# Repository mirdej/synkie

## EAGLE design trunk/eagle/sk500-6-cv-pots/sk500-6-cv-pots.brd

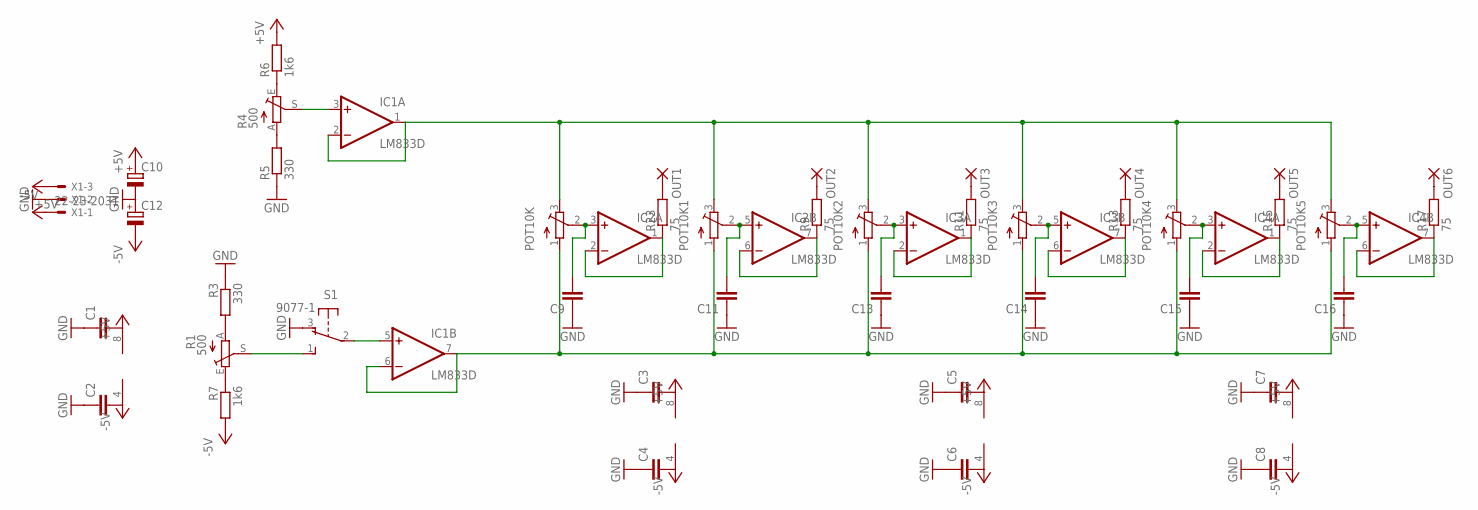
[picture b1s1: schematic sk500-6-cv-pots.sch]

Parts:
C1, C2, C3, C4, C5, C6, C7, C8, C9, C11, C13, C14, C15, C16: C-EUC1206; C1206
C10, C12: CPOL-EUCT6032; CT6032
IC1, IC2, IC3, IC4: LM833D; SO08
OUT1, OUT2, OUT3, OUT4, OUT5, OUT6: 3,17/1,1
POT10K, POT10K1, POT10K2, POT10K3, POT10K4, POT10K5: 10k; ALPS_RK09K111_H
R1, R4: 500; B64W
R3, R5: 330; R1206
R6, R7: 1k6; R1206
R9, R11, R13, R15, R17, R23: 75; R1206
S1: 9077-1
X1: 22-23-2031

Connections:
+5V: C1.2, C3.2, C5.2, C7.2, C10.+, IC1.8 (V+), IC2.8 (V+), IC3.8 (V+), IC4.8 (V+), R6.2, X1.3
-5V: C2.2, C4.2, C6.2, C8.2, C12.-, IC1.4 (V-), IC2.4 (V-), IC3.4 (V-), IC4.4 (V-), R7.2, X1.1
GND: C1.1, C2.1, C3.1, C4.1, C5.1, C6.1, C7.1, C8.1, C9.1, C10.-, C11.1, C12.+, C13.1, C14.1, C15.1, C16.1, R3.1, R5.1, S1.3 (O), X1.2
unnamed: IC1.5 (+IN), S1.2
unnamed: C9.2, IC2.3 (+IN), POT10K.2 (W)
unnamed: R1.A, R3.2
unnamed: R1.E, R7.1
unnamed: R1.S, S1.1 (S)
unnamed: R4.A, R5.2
unnamed: R4.E, R6.1
unnamed: IC1.3 (+IN), R4.S
unnamed: IC1.1 (OUT), IC1.2 (-IN), POT10K.3 (E), POT10K1.3 (E), POT10K2.3 (E), POT10K3.3 (E), POT10K4.3 (E), POT10K5.3 (E)
unnamed: IC2.1 (OUT), IC2.2 (-IN), R23.1
unnamed: OUT2.1, R9.2
unnamed: OUT3.1, R11.2
unnamed: IC2.6 (-IN), IC2.7 (OUT), R9.1
unnamed: IC3.1 (OUT), IC3.2 (-IN), R11.1
unnamed: OUT4.1, R13.2
unnamed: OUT1.1, R23.2
unnamed: IC3.6 (-IN), IC3.7 (OUT), R13.1
unnamed: C11.2, IC2.5 (+IN), POT10K1.2 (W)
unnamed: C13.2, IC3.3 (+IN), POT10K2.2 (W)
unnamed: OUT5.1, R15.2
unnamed: C14.2, IC3.5 (+IN), POT10K3.2 (W)
unnamed: IC4.1 (OUT), IC4.2 (-IN), R15.1
unnamed: IC1.6 (-IN), IC1.7 (OUT), POT10K.1 (S), POT10K1.1 (S), POT10K2.1 (S), POT10K3.1 (S), POT10K4.1 (S), POT10K5.1 (S)
unnamed: OUT6.1, R17.2
unnamed: IC4.6 (-IN), IC4.7 (OUT), R17.1
unnamed: C15.2, IC4.3 (+IN), POT10K4.2 (W)
unnamed: C16.2, IC4.5 (+IN), POT10K5.2 (W)

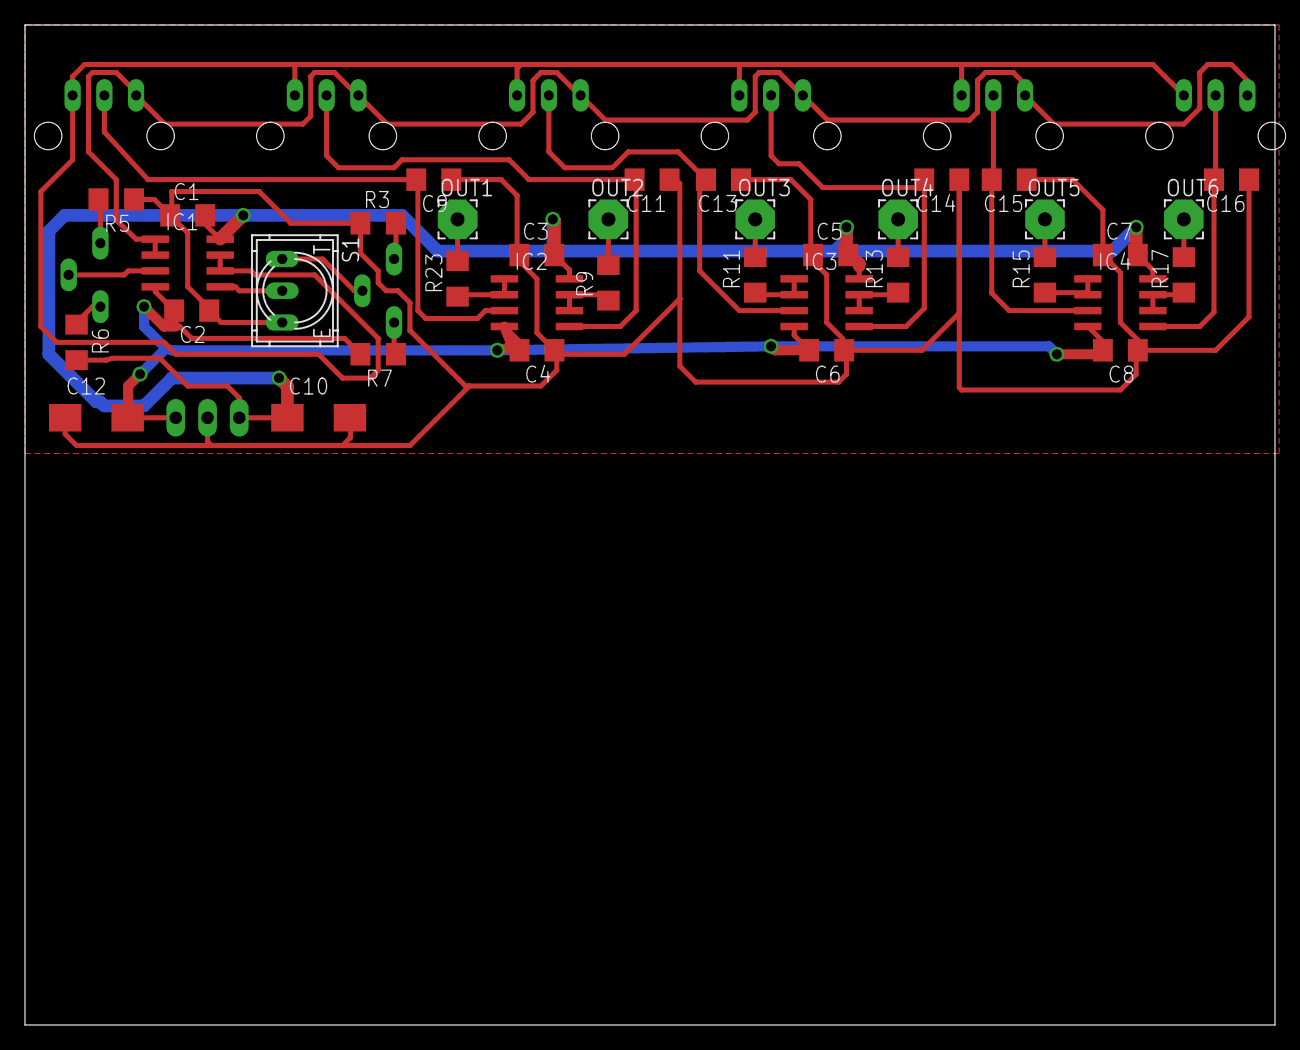
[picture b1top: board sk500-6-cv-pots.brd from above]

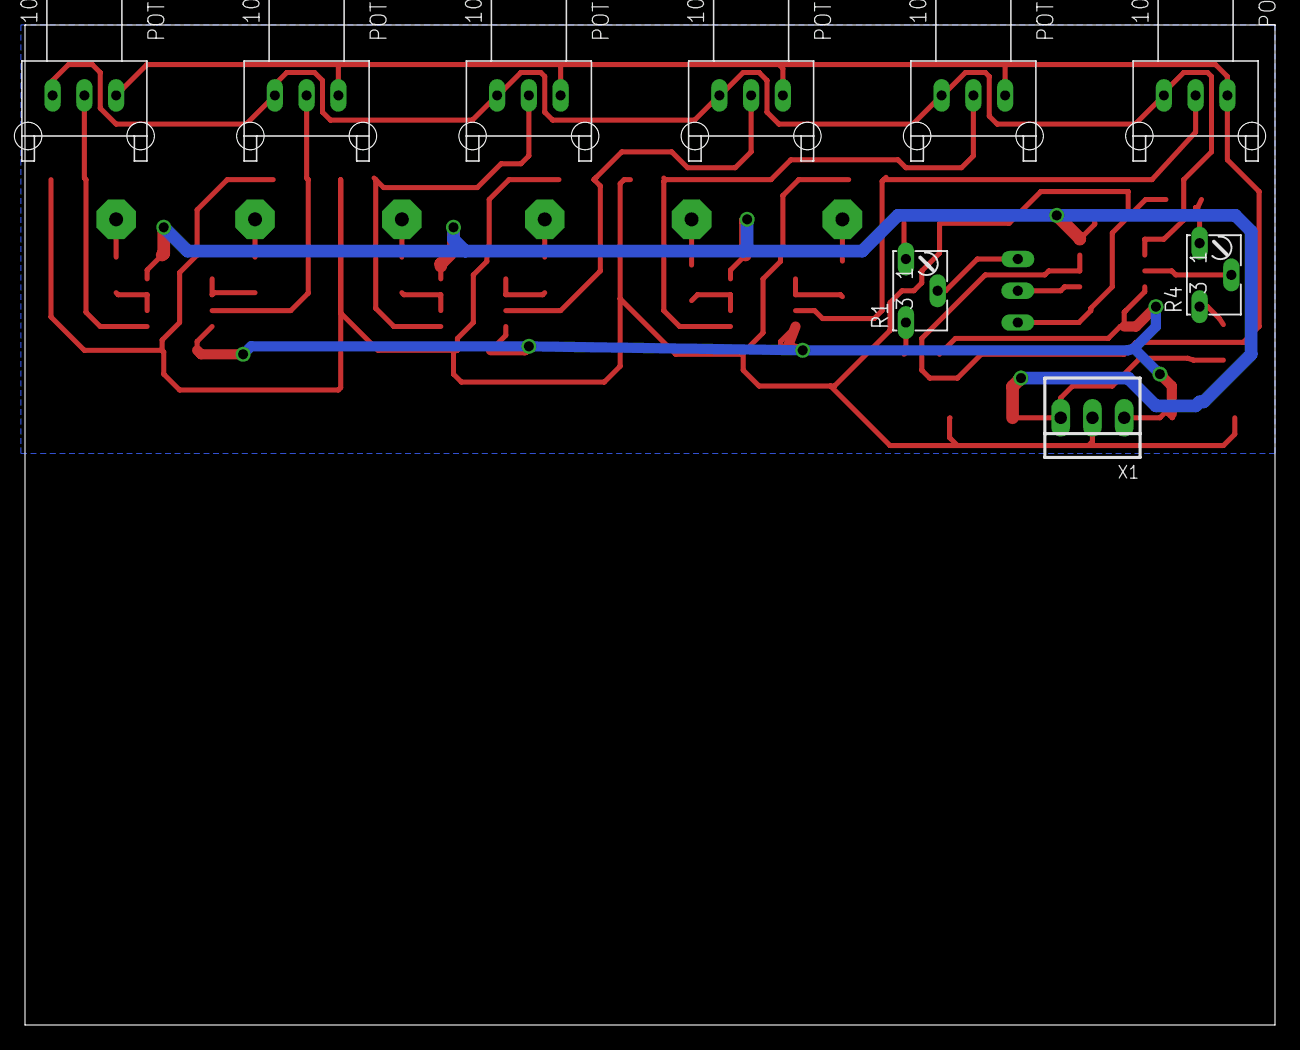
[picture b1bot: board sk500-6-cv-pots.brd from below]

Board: 2 copper layers, 100.0 x 80.0 mm, 46 parts (9 on the bottom side), 30 nets.

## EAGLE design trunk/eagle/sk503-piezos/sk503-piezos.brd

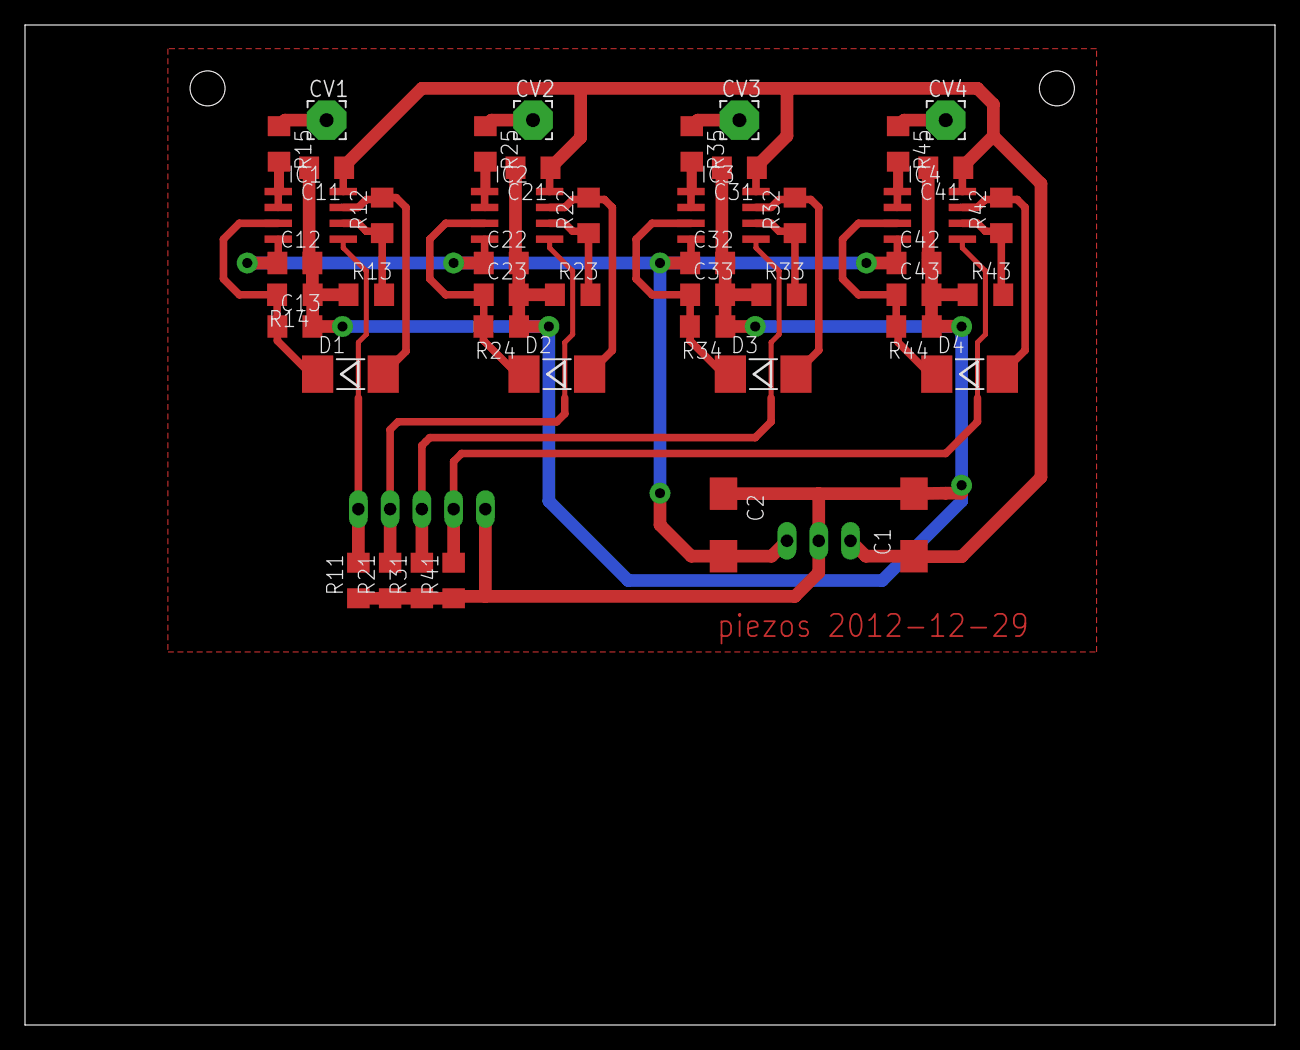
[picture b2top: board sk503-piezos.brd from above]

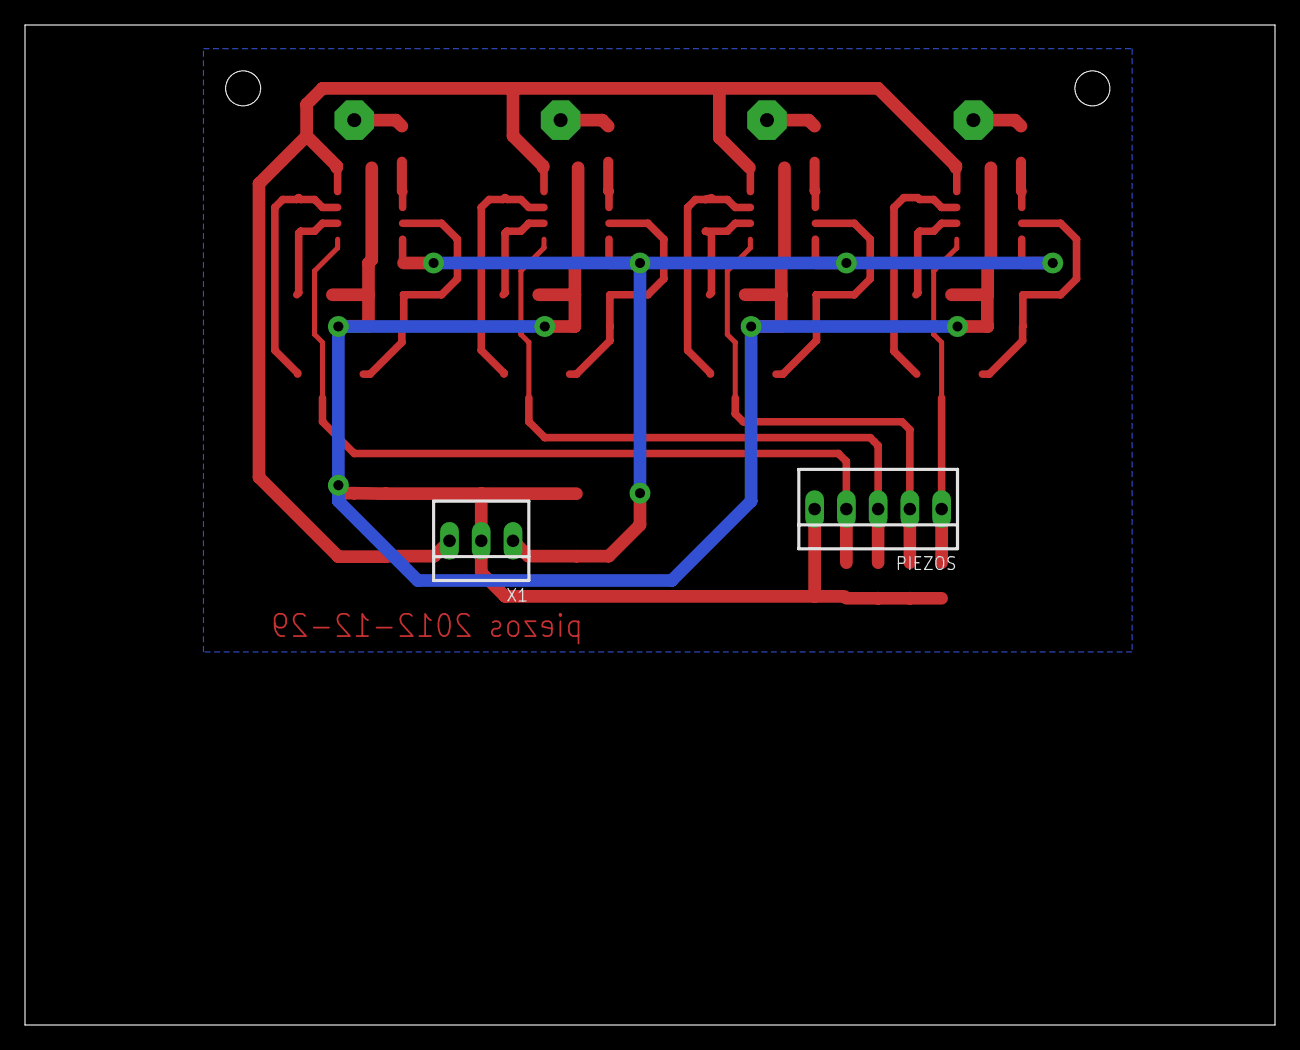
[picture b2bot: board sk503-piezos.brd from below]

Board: 2 copper layers, 100.0 x 80.0 mm, 48 parts (2 on the bottom side), 27 nets.

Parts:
C1, C2: CT6032
C11, C12, C21, C22, C31, C32, C41, C42: C1206
C13, C23, C33, C43: 100n; C1206
CV1, CV2, CV3, CV4: 3,17/1,1
D1, D2, D3, D4: MELF-MLL41
IC1, IC2, IC3, IC4: LM833D; SO08
PIEZOS: 22-23-2051
R11, R21, R31, R41: 20k; R1206
R12, R13, R22, R23, R32, R33, R42, R43: 10k; R1206
R14, R24, R34, R44: 470k; R1206
R15, R25, R35, R45: 75; R1206
X1: 22-23-2031

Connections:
+5V: C1.+, C11.1, C21.1, C31.1, C41.1, IC1.8, IC2.8, IC3.8, IC4.8, X1.3
-5V: C2.-, C12.1, C22.1, C32.1, C42.1, IC1.4, IC2.4, IC3.4, IC4.4, X1.1
GND: C1.-, C2.+, C11.2, C12.2, C13.2, C21.2, C22.2, C23.2, C31.2, C32.2, C33.2, C41.2, C42.2, C43.2, PIEZOS.5, R11.1, R13.1, R14.1, R21.1, R23.1, R24.1, R31.1, R33.1, R34.1, R41.1, R43.1, R44.1, X1.2
unnamed: IC1.5, PIEZOS.1, R11.2
unnamed: D1.A, IC1.7, R12.2
unnamed: IC1.6, R12.1, R13.2
unnamed: IC1.1, IC1.2, R15.2
unnamed: CV1.1, R15.1
unnamed: IC2.5, PIEZOS.2, R21.2
unnamed: IC2.6, R22.1, R23.2
unnamed: C13.1, D1.C, IC1.3, R14.2
unnamed: IC2.1, IC2.2, R25.2
unnamed: CV2.1, R25.1
unnamed: C23.1, D2.C, IC2.3, R24.2
unnamed: IC3.5, PIEZOS.3, R31.2
unnamed: D3.A, IC3.7, R32.2
unnamed: IC3.6, R32.1, R33.2
unnamed: IC3.1, IC3.2, R35.2
unnamed: CV3.1, R35.1
unnamed: C33.1, D3.C, IC3.3, R34.2
unnamed: IC4.5, PIEZOS.4, R41.2
unnamed: IC4.6, R42.1, R43.2
unnamed: IC4.1, IC4.2, R45.2
unnamed: CV4.1, R45.1
unnamed: C43.1, D4.C, IC4.3, R44.2
unnamed: D2.A, IC2.7, R22.2
unnamed: D4.A, IC4.7, R42.2

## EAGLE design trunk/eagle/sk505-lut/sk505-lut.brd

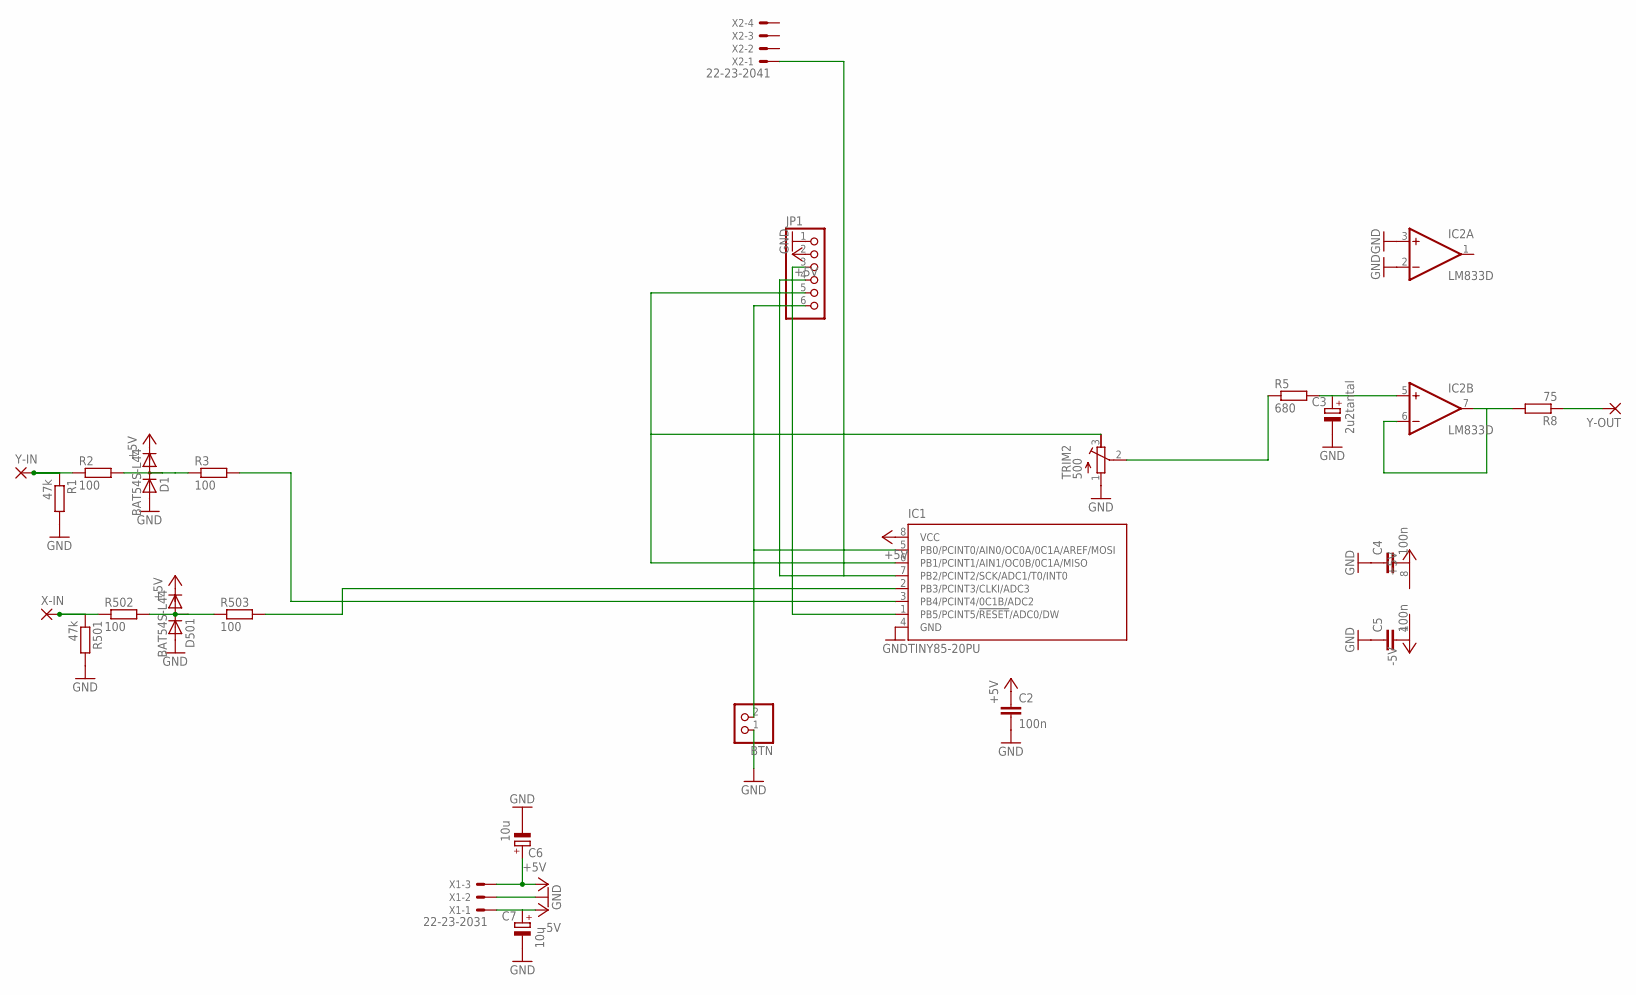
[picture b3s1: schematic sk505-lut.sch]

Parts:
BTN: PINHD-1X2; 1X02
C2: 100n; C1206
C3: 2u2tantal; CT3528
C4, C5: 100n; C0603
C6, C7: 10u; CT3528
D1, D501: BAT54S-L44; SOT23
IC1: TINY85-20PU; DIL08; MPN ATTINY13-20PU
IC2: LM833D; SO08
JP1: PINHD-1X6; 1X06
R1, R501: 47k; R1206
R2, R3, R502, R503: 100; R1206
R5: 680; R1206
R8: 75; R1206
TRIM2: 500; RTRIM64Y
X1: 22-23-2031
X2: 22-23-2041
X-IN: 3,17/1,1
Y-IN: 3,17/1,1
Y-OUT: 3,17/1,1

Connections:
+5V: C2.1, C4.2, C6.+, D1.2 (C), D501.2 (C), IC1.8 (VCC), IC2.8 (V+), JP1.2, X1.3
-5V: C5.2, C7.+, IC2.4 (V-), X1.1
GND: BTN.1, C2.2, C3.-, C4.1, C5.1, C6.-, C7.-, D1.1 (A), D501.1 (A), IC1.4 (GND), IC2.2 (-IN), IC2.3 (+IN), JP1.1, R1.2, R501.2, TRIM2.1 (E), X1.2
unnamed: IC1.1 (PB5/PCINT5/!RESET!/ADC0/DW), JP1.3
unnamed: IC1.7 (PB2/PCINT2/SCK/ADC1/T0/INT0), JP1.4, X2.1
unnamed: IC1.6 (PB1/PCINT1/AIN1/OC0B/0C1A/MISO), JP1.5, TRIM2.3 (A)
unnamed: BTN.2, IC1.5 (PB0/PCINT0/AIN0/OC0A/0C1A/AREF/MOSI), JP1.6
unnamed: R1.1, R2.1, Y-IN.1
unnamed: D1.3 (AC), R2.2, R3.1
unnamed: IC1.3 (PB4/PCINT4/0C1B/ADC2), R3.2
unnamed: IC1.2 (PB3/PCINT3/CLKI/ADC3), R503.2
unnamed: C3.+, IC2.5 (+IN), R5.2
unnamed: R501.1, R502.1, X-IN.1
unnamed: D501.3 (AC), R502.2, R503.1
unnamed: R8.1, Y-OUT.1
unnamed: R5.1, TRIM2.2 (S)
unnamed: IC2.6 (-IN), IC2.7 (OUT), R8.2

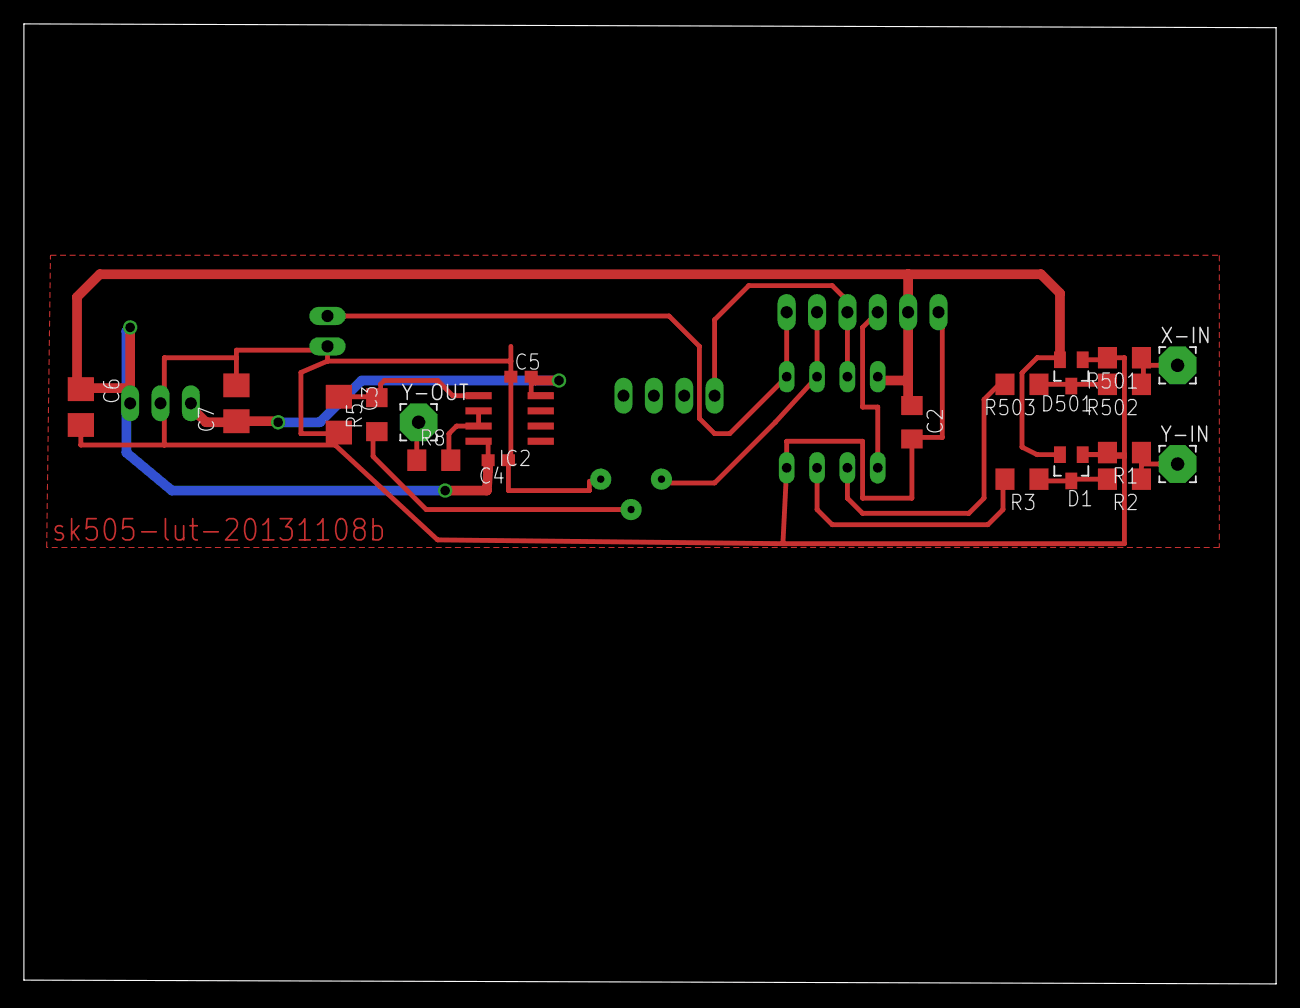
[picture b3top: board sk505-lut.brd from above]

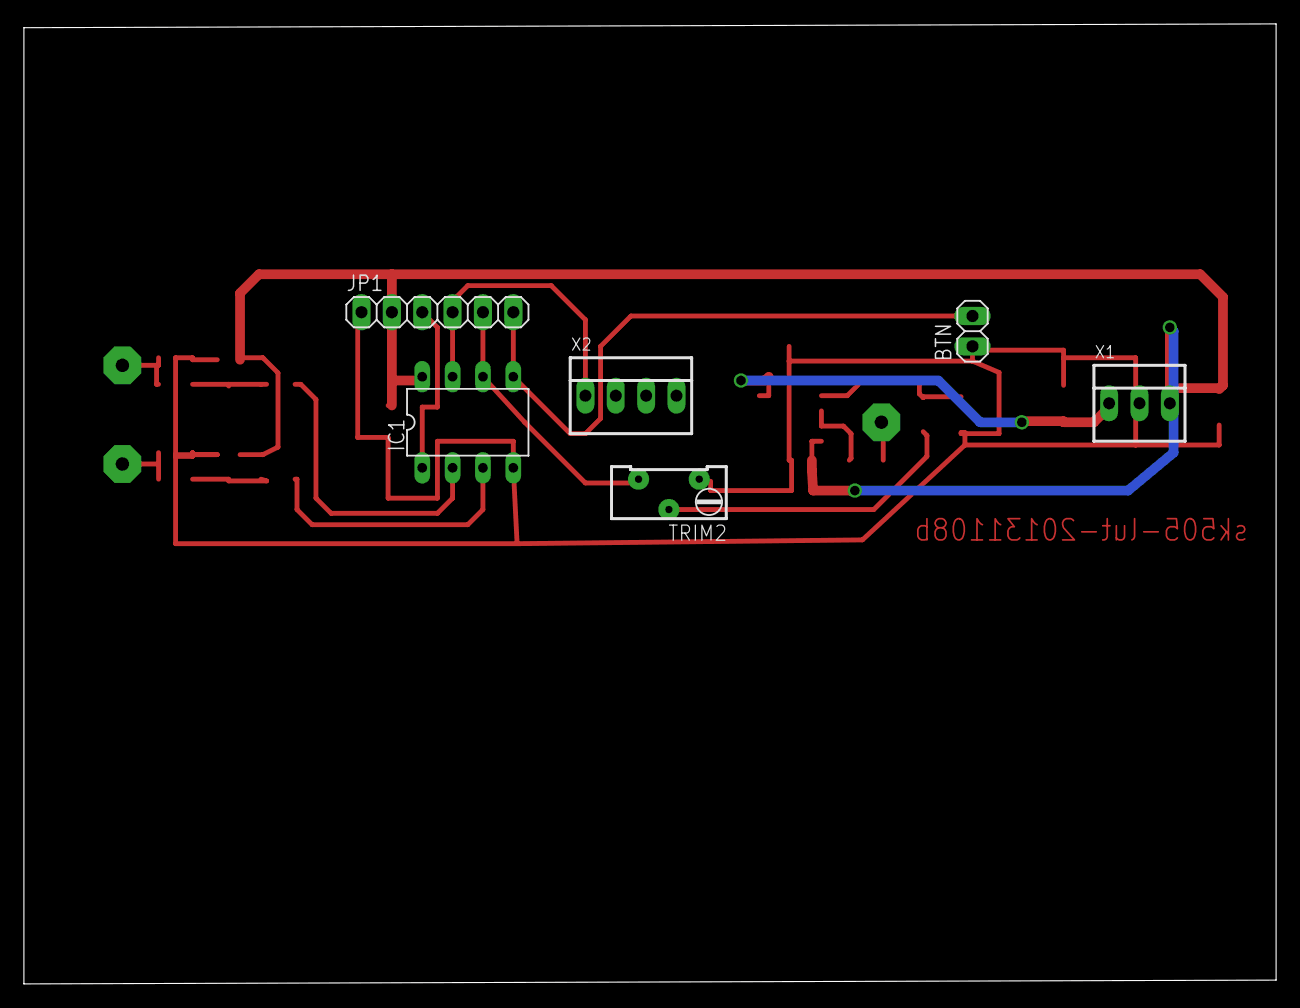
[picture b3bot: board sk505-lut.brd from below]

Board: 2 copper layers, 104.8 x 80.3 mm, 26 parts (6 on the bottom side), 17 nets.

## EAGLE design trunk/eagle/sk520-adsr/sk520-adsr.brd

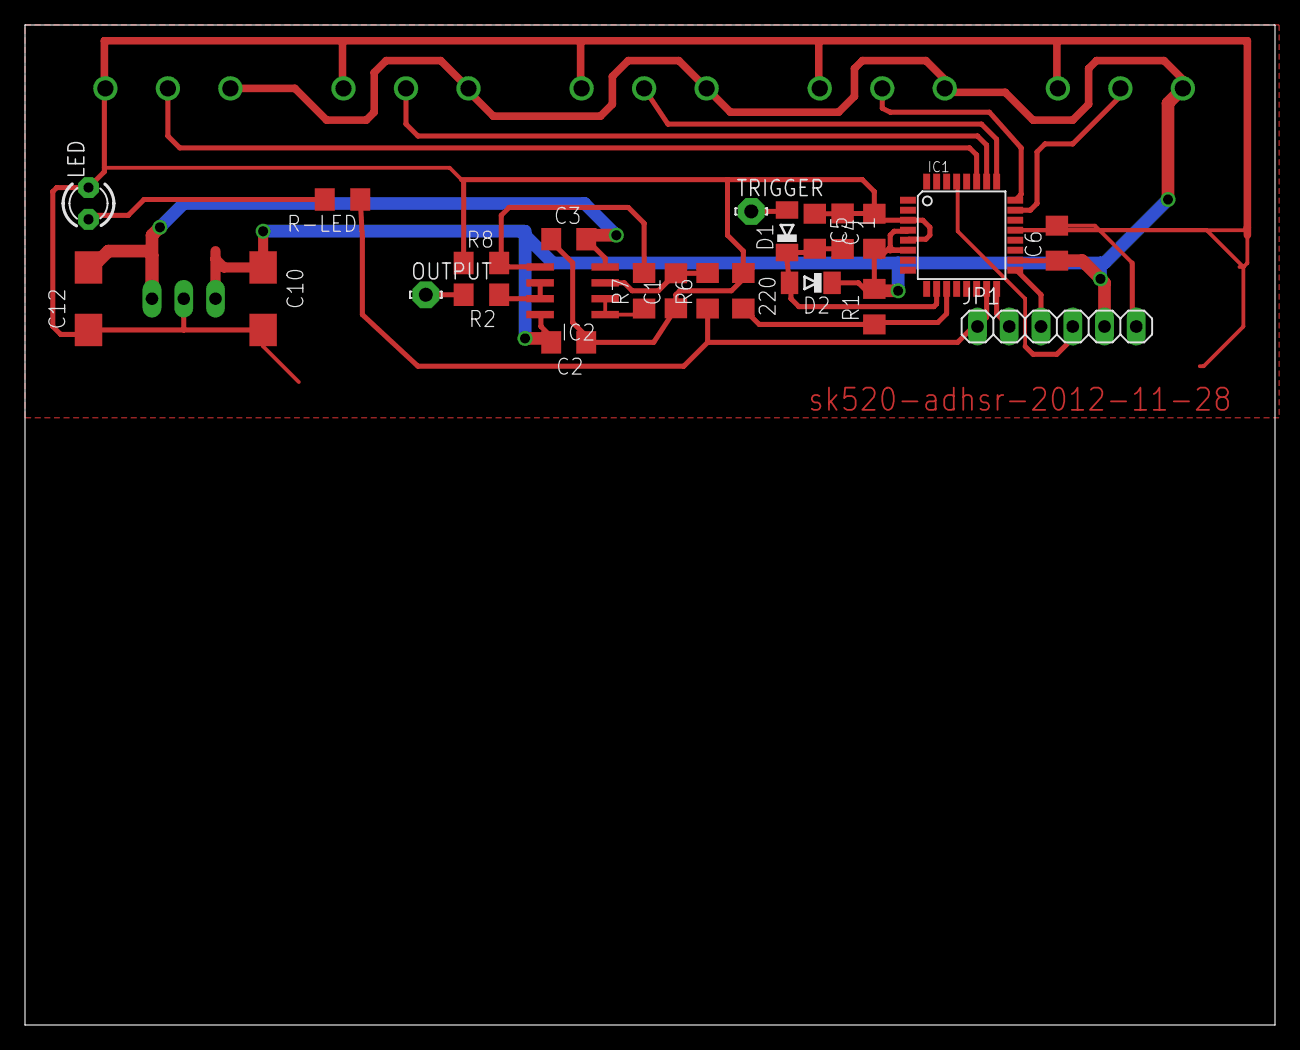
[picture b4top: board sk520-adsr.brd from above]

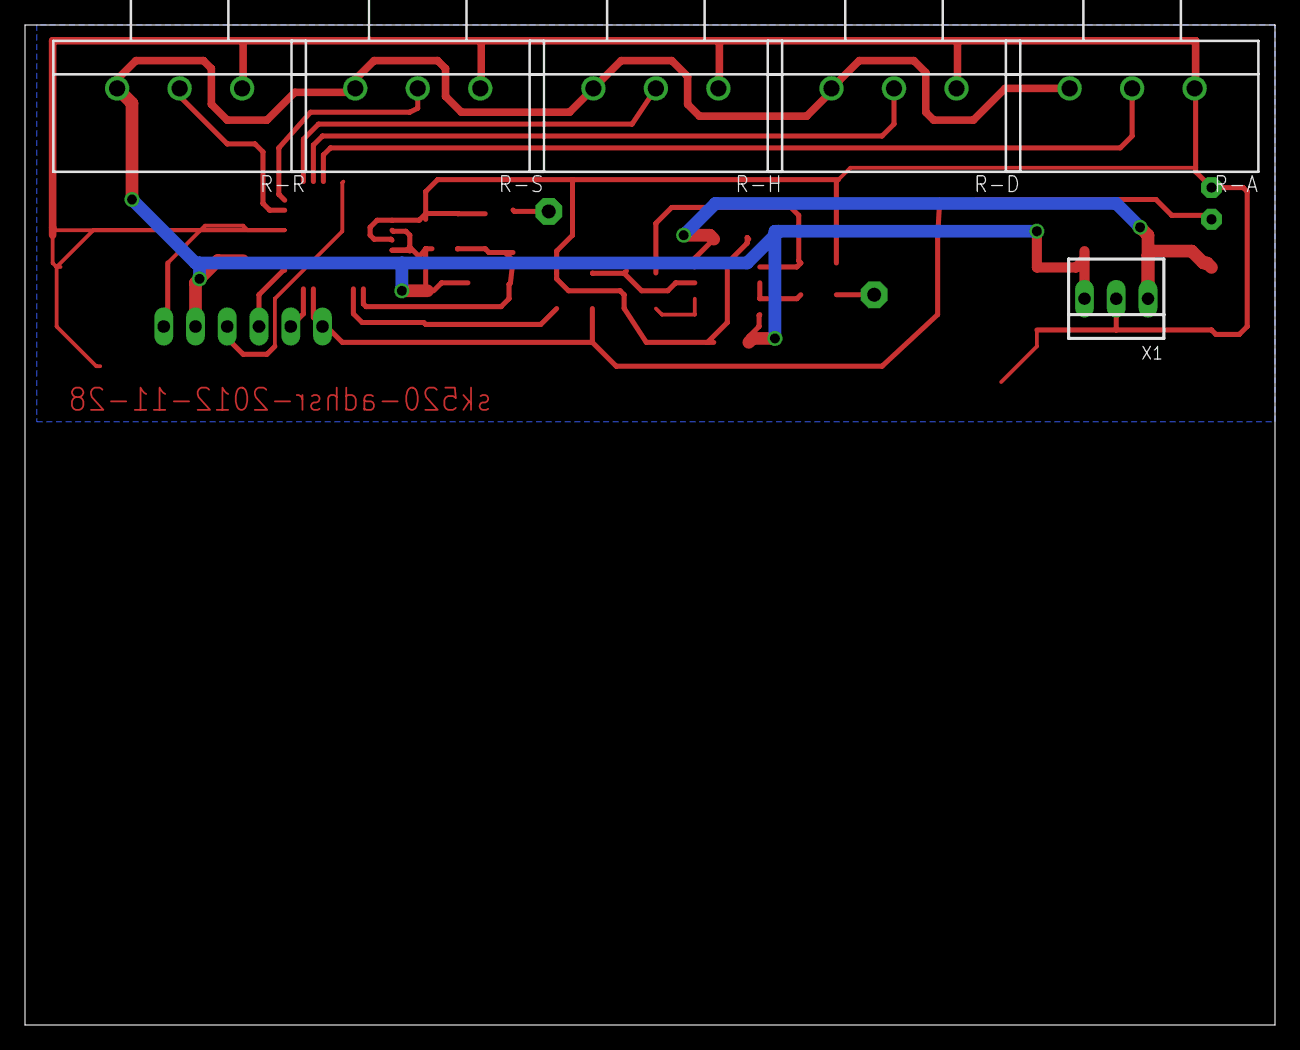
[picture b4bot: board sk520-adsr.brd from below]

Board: 2 copper layers, 100.0 x 80.0 mm, 30 parts (6 on the bottom side), 21 nets.

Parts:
1: 47k; R1206
220: 100; R1206
C1, C5: 100n; C1206
C2, C3, C4, C6: C1206
C10, C12: CT6032
D1, D2: MINIMELF
IC1: MEGA8-AI; TQFP32-08
IC2: LM833D; SO08
JP1: 1X06
LED: LED3MM
OUTPUT: LSP11
R1, R8: 1k; R1206
R2: 75; R1206
R6: 10k; R1206
R7: 3k; R1206
R-A: 100k; CIP20C-6MM
R-D: 100k; CIP20C-6MM
R-H: 100k; CIP20C-6MM
R-LED: 1k; R1206
R-R: 100k; CIP20C-6MM
R-S: 100k; CIP20C-6MM
TRIGGER: LSP11
X1: 22-23-2031

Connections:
+5V: C2.2, C4.1, C6.1, C10.+, D2.C, IC1.4, IC1.6, IC1.18, IC2.8, JP1.5, R1.2, R-A.E, R-D.E, R-H.E, R-R.E, R-S.E, X1.3
-5V: C3.2, C12.-, IC2.4, X1.1
GND: 1.1, 220.1, C1.1, C2.1, C3.1, C4.2, C5.1, C6.2, C10.-, C12.+, IC1.3, IC1.5, IC1.21, JP1.6, LED.K, R8.1, R-A.A, R-D.A, R-H.A, R-R.A, R-S.A, X1.2
unnamed: IC1.15, JP1.1, R6.1, R-LED.1
unnamed: D1.A, TRIGGER.MP
unnamed: IC1.16, JP1.2
unnamed: IC1.17, JP1.3
unnamed: IC1.29, JP1.4
unnamed: IC1.27, R-A.S
unnamed: IC1.26, R-D.S
unnamed: IC1.25, R-H.S
unnamed: IC1.24, R-S.S
unnamed: IC1.23, R-R.S
unnamed: 1.2, C5.2, D1.C, D2.A, IC1.10
unnamed: C1.2, IC2.3, R6.2
unnamed: IC2.1, IC2.2, R7.1
unnamed: IC2.5, R7.2, R8.2
unnamed: IC2.6, IC2.7, R2.1
unnamed: 220.2, IC1.11, R1.1
unnamed: OUTPUT.MP, R2.2
unnamed: LED.A, R-LED.2

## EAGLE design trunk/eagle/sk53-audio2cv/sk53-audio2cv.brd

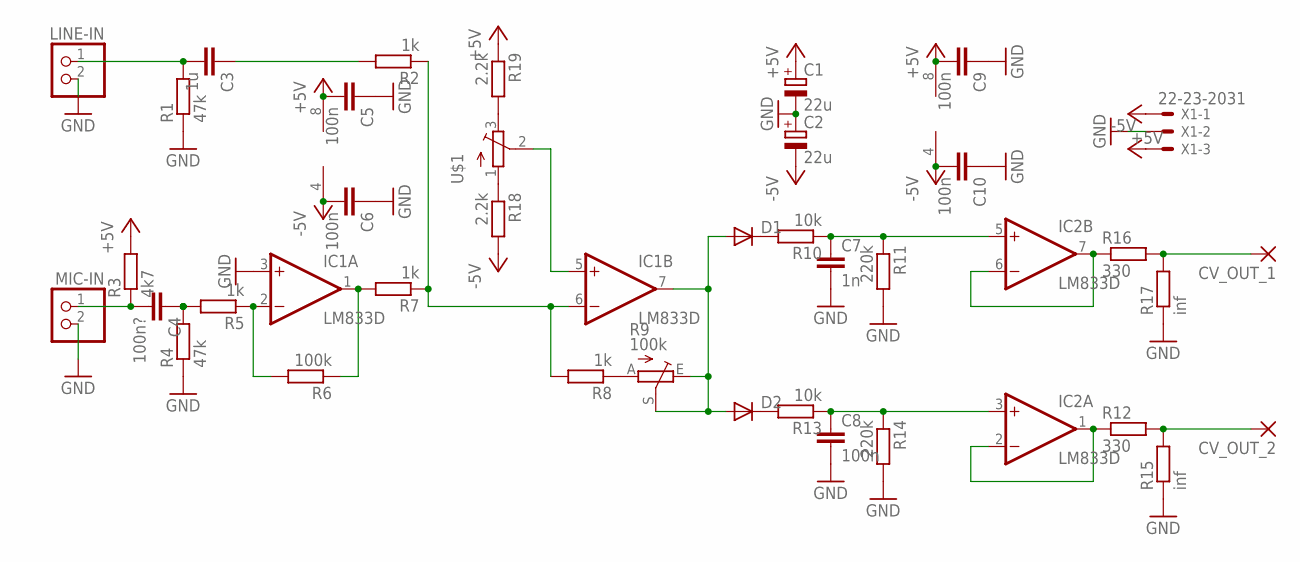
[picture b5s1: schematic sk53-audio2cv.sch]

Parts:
C1, C2: 22u; CT3528
C3: 1u; C1206
C4: 100n?; C1206
C5, C6, C8, C9, C10: 100n; C1206
C7: 1n; C1206
CV_OUT_1, CV_OUT_2: 3,17/1,1
D1, D2: DIODE-SMB; SMB
IC1, IC2: LM833D; SO08
LINE-IN: PINHD-1X2; 1X02
MIC-IN: PINHD-1X2; 1X02
R1, R4: 47k; R1206
R2, R5, R7, R8: 1k; R1206
R3: 4k7; R1206
R6: 100k; R1206
R9: 100k; CIP20C-6MM
R10, R13: 10k; R1206
R11, R14: 220k; R1206
R12, R16: 330; R1206
R15, R17: inf; R1206
R18, R19: 2.2k; R1206
U$1: 1k; ALPS_RK09K111
X1: 22-23-2031

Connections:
+5V: C1.+, C5.2, C9.2, IC1.8 (V+), IC2.8 (V+), R3.2, R19.1, X1.1
-5V: C2.-, C6.2, C10.2, IC1.4 (V-), IC2.4 (V-), R18.2, X1.3
GND: C1.-, C2.+, C5.1, C6.1, C7.2, C8.2, C9.1, C10.1, IC1.3 (+IN), LINE-IN.2, MIC-IN.2, R1.1, R4.1, R11.2, R14.2, R15.1, R17.1, X1.2
unnamed: C3.2, LINE-IN.1, R1.2
unnamed: C3.1, R2.2
unnamed: C4.2, MIC-IN.1, R3.1
unnamed: C4.1, R4.2, R5.2
unnamed: IC1.2 (-IN), R5.1, R6.2
unnamed: IC1.1 (OUT), R6.1, R7.2
unnamed: R19.2, U$1.3 (E)
unnamed: R8.1, R9.A
unnamed: D1.A, D2.A, IC1.7 (OUT), R9.E, R9.S
unnamed: D1.C, R10.2
unnamed: C7.1, IC2.5 (+IN), R10.1, R11.1
unnamed: IC2.6 (-IN), IC2.7 (OUT), R16.1
unnamed: CV_OUT_2.1, R12.2, R15.2
unnamed: D2.C, R13.2
unnamed: C8.1, IC2.3 (+IN), R13.1, R14.1
unnamed: IC2.1 (OUT), IC2.2 (-IN), R12.1
unnamed: CV_OUT_1.1, R16.2, R17.2
unnamed: R18.1, U$1.1 (S)
unnamed: IC1.5 (+IN), U$1.2 (W)
unnamed: IC1.6 (-IN), R2.1, R7.1, R8.2

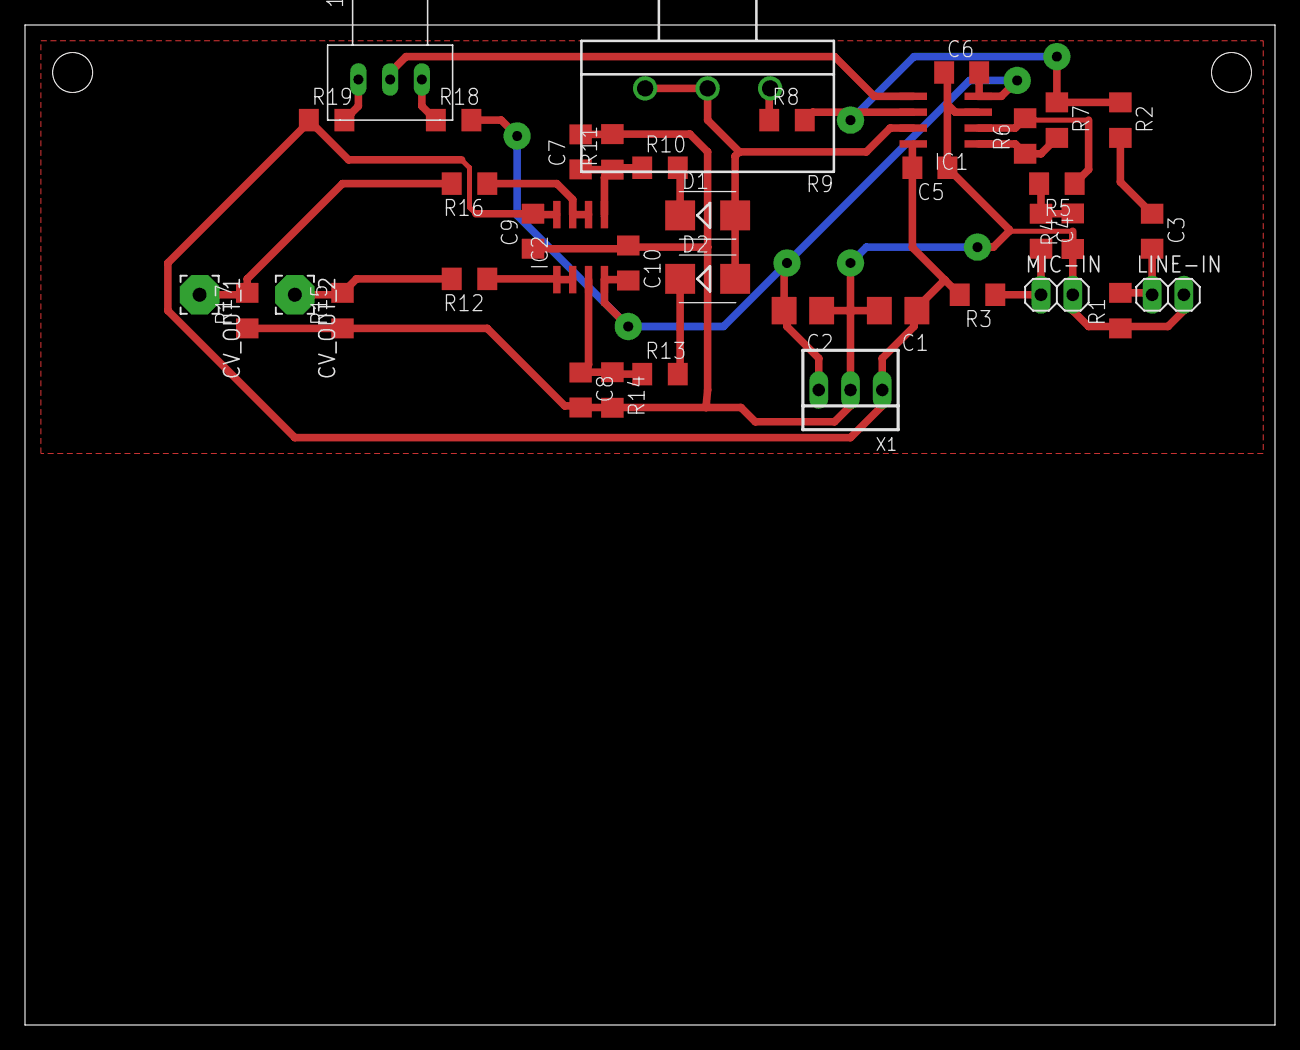
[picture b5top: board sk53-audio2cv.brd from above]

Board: 2 copper layers, 100.0 x 80.0 mm, 39 parts (0 on the bottom side), 23 nets.
